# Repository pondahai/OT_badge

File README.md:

# OT_badge
Electronic badges can be used for soldering practice. From Openlab Taipei.

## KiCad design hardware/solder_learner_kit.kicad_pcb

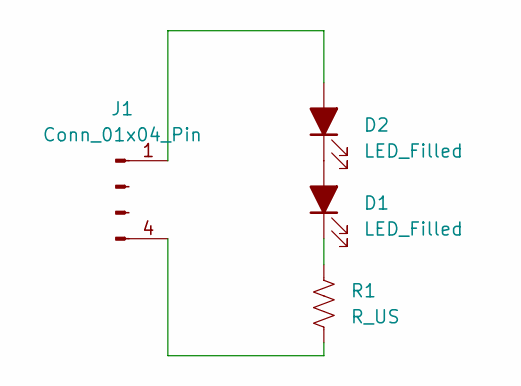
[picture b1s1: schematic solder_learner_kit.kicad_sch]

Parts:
D1, D2: LED_Filled; LED_D3.0mm
J1: Conn_01x04_Pin; usb-PCB
R1: R_US; R_Axial_DIN0204_L3.6mm_D1.6mm_P7.62mm_Horizontal

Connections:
unnamed: D1.2 (A), D2.1 (K)
unnamed: D1.1 (K), R1.1
unnamed: D2.2 (A), J1.1
unnamed: J1.4, R1.2

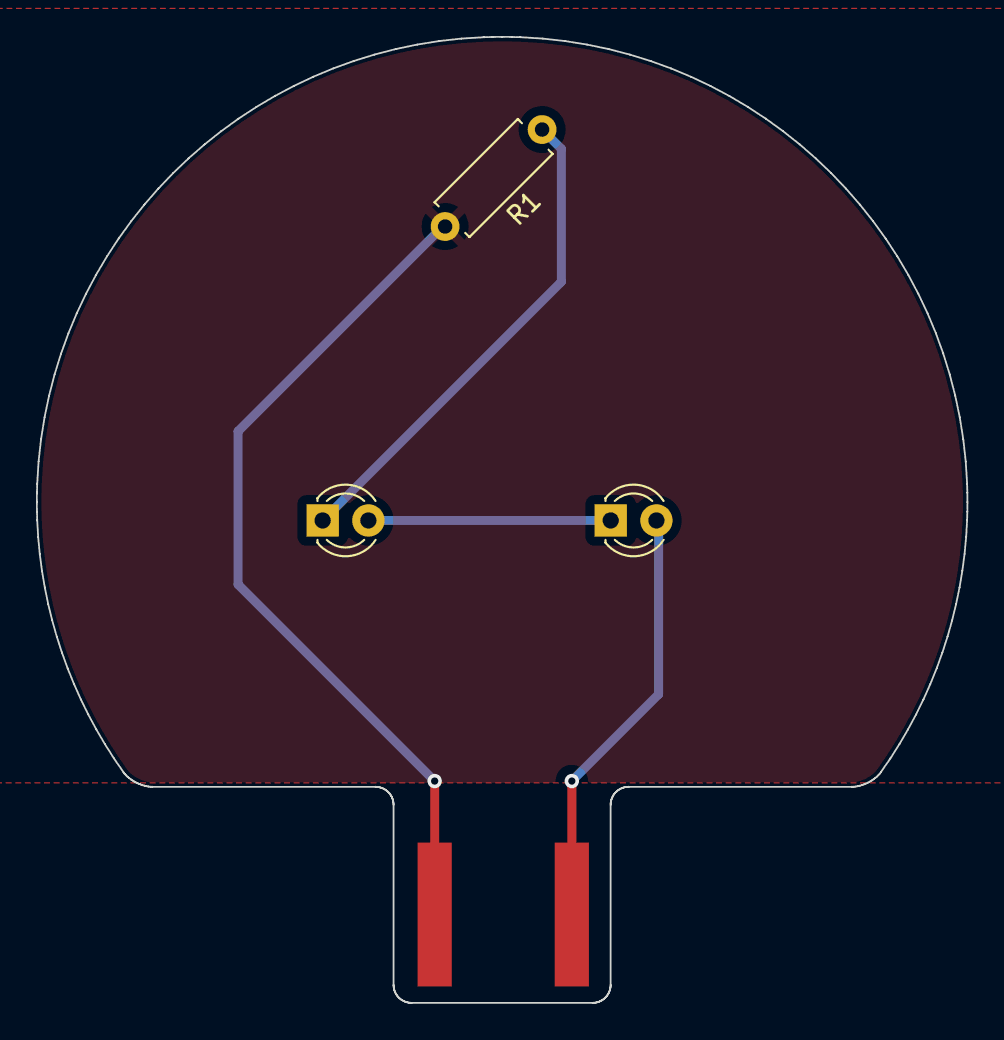
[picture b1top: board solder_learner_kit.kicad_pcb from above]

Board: 2 copper layers, 51.7 x 53.7 mm, 4 parts (0 on the bottom side), 4 nets.
